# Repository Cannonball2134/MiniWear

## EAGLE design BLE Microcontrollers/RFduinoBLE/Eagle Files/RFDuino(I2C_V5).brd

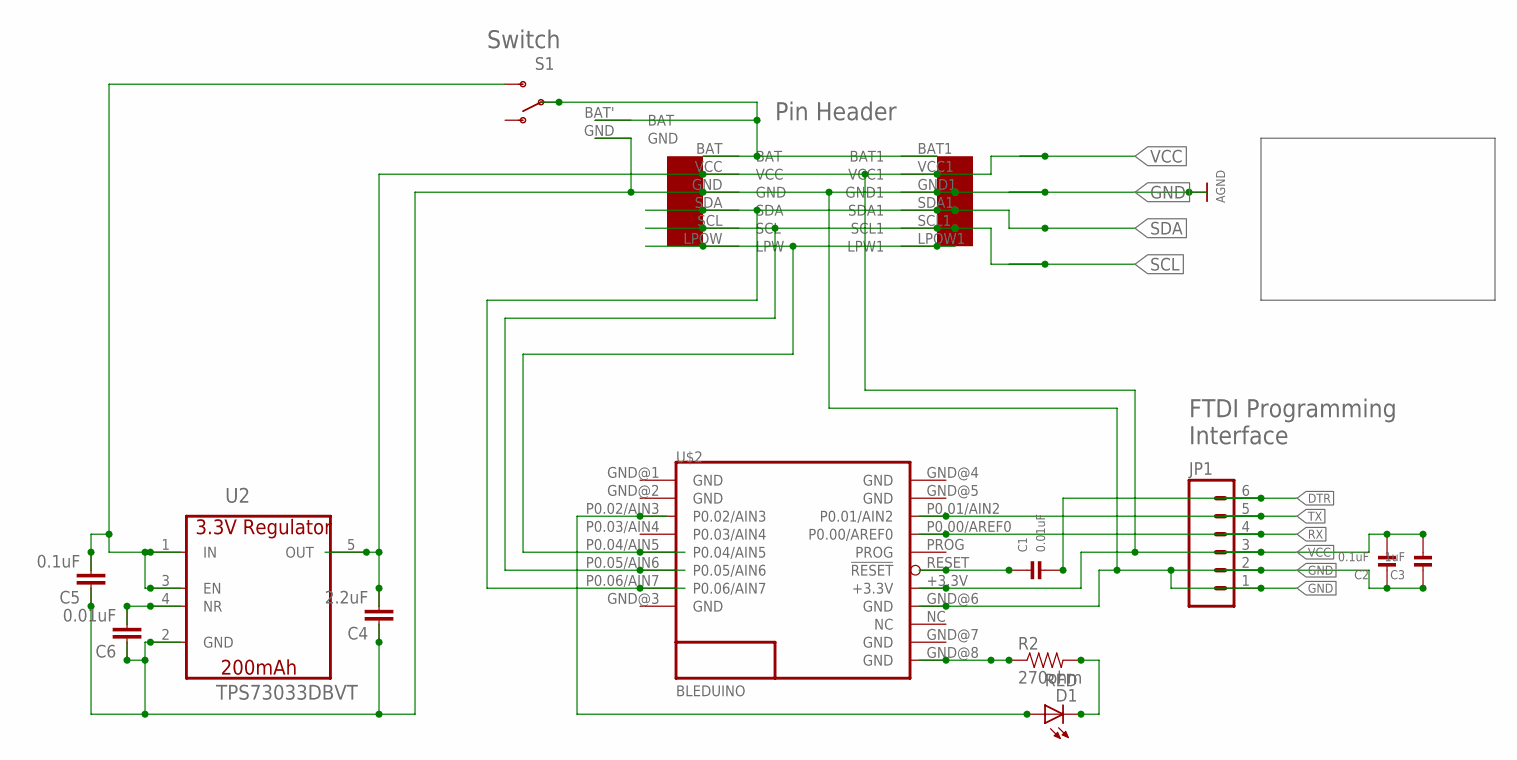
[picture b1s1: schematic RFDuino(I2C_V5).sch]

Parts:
C1: 0.01uF; 0402
C2: 0.1uF; 0402
C3: 1uF; 0402
C4: 2.2uF; 0402-CAP
C5: 0.1uF; 0402-CAP
C6: 0.01uF; 0402-CAP
D1: RED; LED-0603
JP1: M06SIP; 1X06
R2: 270ohm; 0402-RES
S1: SWITCH-SPDT-SMD-A; SWITCH-SPST-SMD-A
U2: TPS73033DBVT; SOT95P290X145-5N
U$1: EZ-I2CHEADERV1
U$2: BLEDUINO
U$4: MINI_BATTERY_HOLES

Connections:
BAT: S1.2, U$1.BAT, U$1.BAT1, U$4.BAT' (BAT)
BAT_INPUT: C5.2, S1.3 (S), U2.1 (IN), U2.3 (EN)
DTR: C1.2, JP1.6
GND: C2.1, C3.1, C4.1, C5.1, C6.1, JP1.1, JP1.2, U2.2 (GND), U$1.GND, U$1.GND1, U$2.GND@6 (GND), U$4.GND
LPW: U$1.LPOW (LPW), U$1.LPOW1 (LPW1), U$2.P0.04/AIN5
unnamed: C1.1, U$2.RESET (!RESET)
unnamed: D1.A, U$2.P0.02/AIN3
unnamed: C6.2, U2.4 (NR)
unnamed: D1.C, R2.2
unnamed: R2.1, U$2.GND@8 (GND)
RX: JP1.4, U$2.P0.00/AREF0
SCL: U$1.SCL, U$1.SCL1, U$2.P0.05/AIN6
SDA: U$1.SDA, U$1.SDA1, U$2.P0.06/AIN7
TX: JP1.5, U$2.P0.01/AIN2
VCC: C2.2, C3.2, C4.2, JP1.3, U2.5 (OUT), U$1.VCC, U$1.VCC1, U$2.+3.3V

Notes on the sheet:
Switch
Pin Header
FTDI Programming Interface

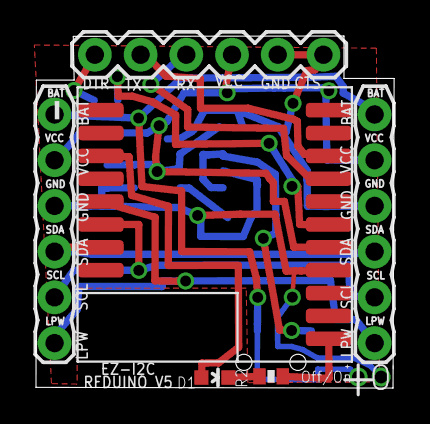
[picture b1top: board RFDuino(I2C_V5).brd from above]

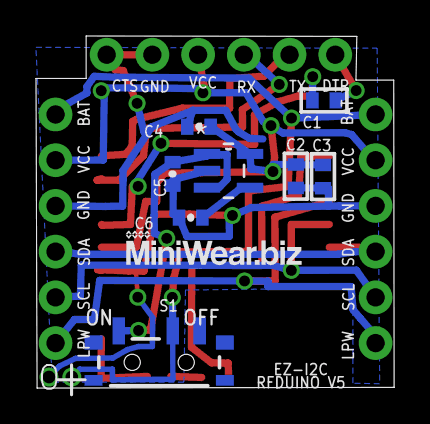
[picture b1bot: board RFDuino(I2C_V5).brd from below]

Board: 2 copper layers, 19.9 x 19.6 mm, 15 parts (9 on the bottom side), 15 nets.

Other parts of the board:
U$3: LOGO2

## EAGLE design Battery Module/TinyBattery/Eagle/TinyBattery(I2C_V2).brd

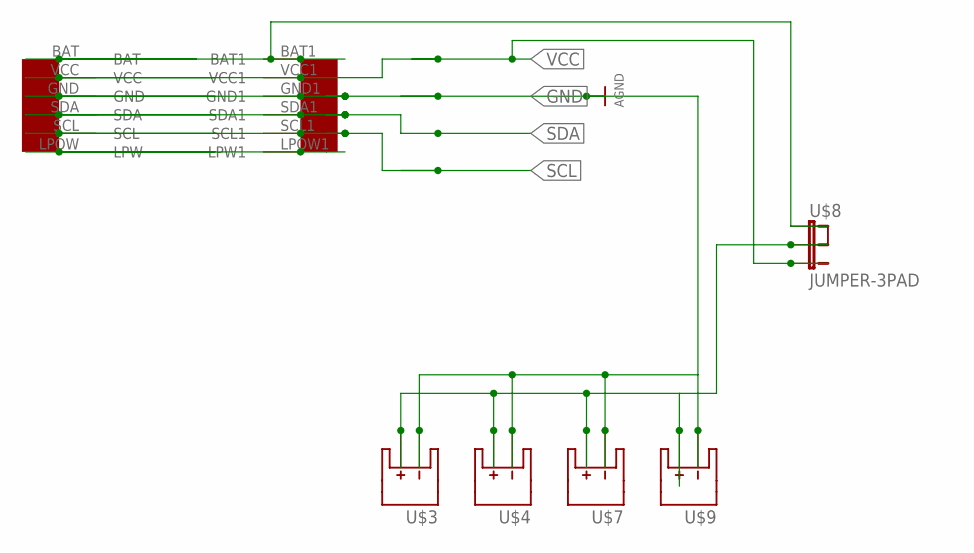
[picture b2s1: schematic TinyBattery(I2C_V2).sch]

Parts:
U$1: EZ-I2CHEADERV1
U$3, U$4, U$7, U$9: BATTERY_1.25MM_PINHOLES
U$8: JUMPER-3PAD

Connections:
BAT: U$1.BAT, U$1.BAT1, U$8.1
GND: U$1.GND, U$1.GND1, U$3.-, U$4.-, U$7.-, U$9.-
unnamed: U$3.+, U$4.+, U$7.+, U$8.2, U$9.+
unnamed: U$1.LPOW (LPW), U$1.LPOW1 (LPW1)
SCL: U$1.SCL, U$1.SCL1
SDA: U$1.SDA, U$1.SDA1
VCC: U$1.VCC, U$1.VCC1, U$8.3

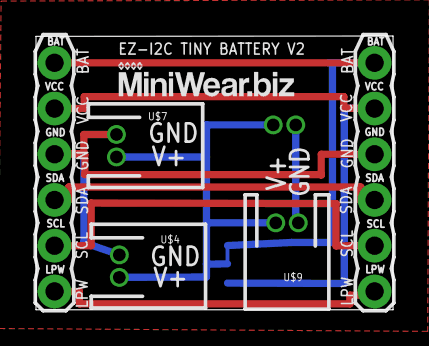
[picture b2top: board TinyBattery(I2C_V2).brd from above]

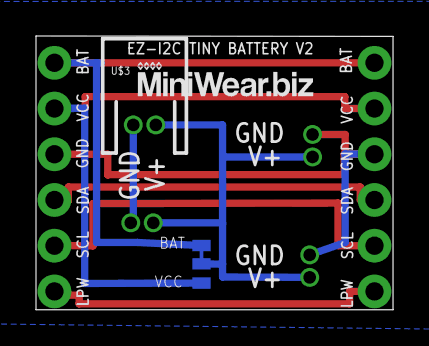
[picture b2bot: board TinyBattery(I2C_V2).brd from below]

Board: 2 copper layers, 19.8 x 15.2 mm, 8 parts (3 on the bottom side), 7 nets.

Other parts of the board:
U$2, U$6: LOGO2

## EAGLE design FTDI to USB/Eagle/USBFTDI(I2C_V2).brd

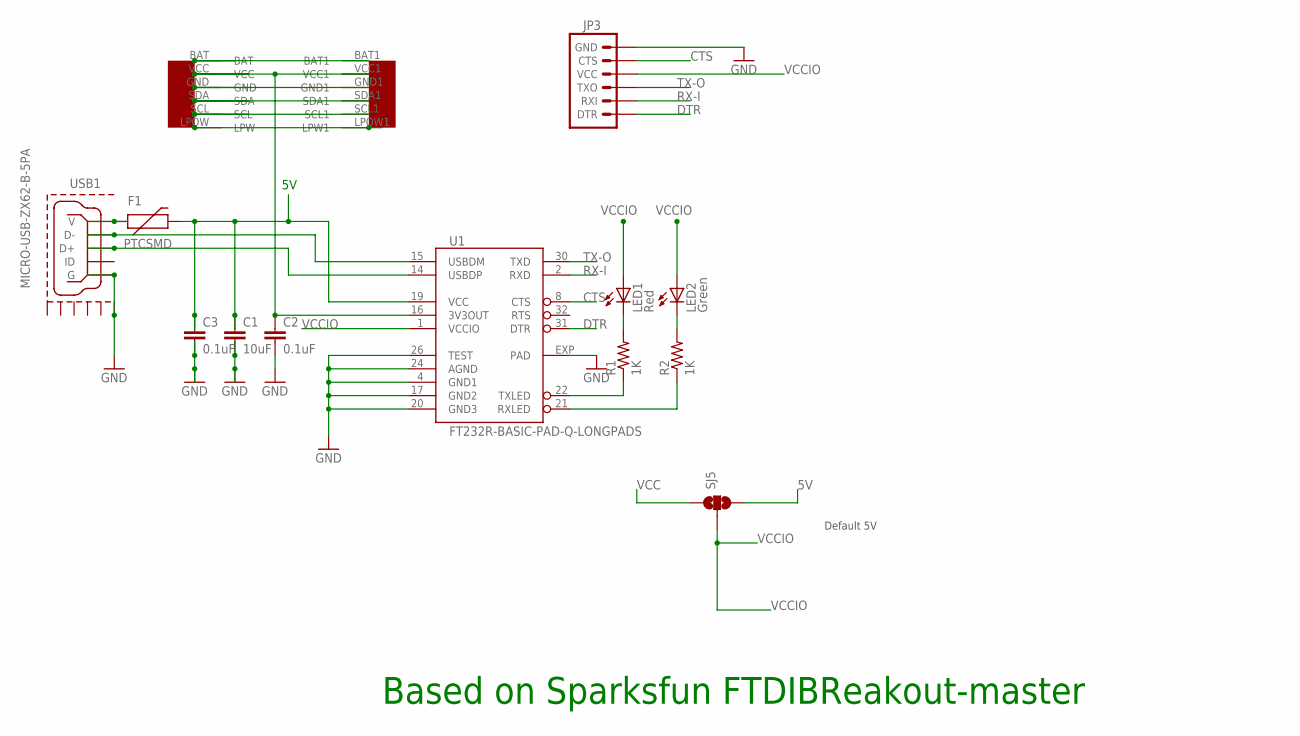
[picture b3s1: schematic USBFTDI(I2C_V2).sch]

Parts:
C1: 10uF; 0402-CAP
C2, C3: 0.1uF; 0402-CAP
F1: PTCSMD; PTC-1206
JP3: ARDUINO_SERIAL_PROGRAMPTH; 1X06
LED1: Red; LED-0603
LED2: Green; LED-0603
R1, R2: 1K; R0402
SJ5: SOLDERJUMPER_2WAY-LEFT-BRIDGED; SJ-3-LEFT
U1: FT232R-BASIC-PAD-Q-LONGPADS; QFN32-LONG
U$1: EZ-I2CHEADERV1
USB1: MICRO-USB-ZX62-B-5PA; ZX62-B-5PA

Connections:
5V: C1.1, C3.1, F1.2, SJ5.3, U1.19 (VCC)
BAT: U$1.BAT, U$1.BAT1
CTS: JP3.5 (CTS), U1.8 (CTS)
DTR: JP3.1 (DTR), U1.31 (DTR)
GND: C1.2, C2.2, C3.2, JP3.6 (GND), U1.4 (GND1), U1.17 (GND2), U1.20 (GND3), U1.24 (AGND), U1.26 (TEST), U1.EXP (PAD), U$1.GND, U$1.GND1, USB1.5 (G), USB1.GND@6 (GND6)
GND1: USB1.GND@1 (GND1)
GND2: USB1.GND@2 (GND2)
GND3: USB1.GND@3 (GND3)
GND4: USB1.GND@4 (GND4)
GND5: USB1.GND@5 (GND5)
LPW: U$1.LPOW (LPW), U$1.LPOW1 (LPW1)
unnamed: U1.14 (USBDP), USB1.3 (D+)
unnamed: U1.15 (USBDM), USB1.2 (D-)
unnamed: R2.1, U1.21 (RXLED)
unnamed: F1.1, USB1.1 (V)
unnamed: LED1.C, R1.2
unnamed: LED2.C, R2.2
unnamed: R1.1, U1.22 (TXLED)
RX-I: JP3.2 (RXI), U1.2 (RXD)
SCL: U$1.SCL, U$1.SCL1
SDA: U$1.SDA, U$1.SDA1
TX-O: JP3.3 (TXO), U1.30 (TXD)
VCC: C2.1, SJ5.1, U1.16 (3V3OUT), U$1.VCC, U$1.VCC1
VCCIO: JP3.4 (VCC), LED1.A, LED2.A, SJ5.2, U1.1 (VCCIO)

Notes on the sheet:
Based on Sparksfun FTDIBReakout-master
Default 5V
VCCIO

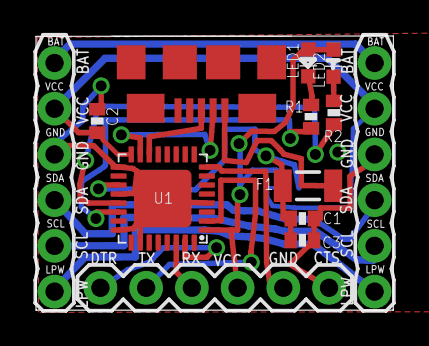
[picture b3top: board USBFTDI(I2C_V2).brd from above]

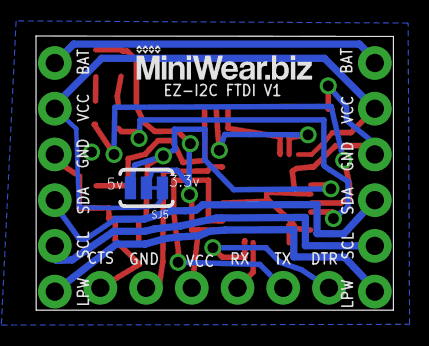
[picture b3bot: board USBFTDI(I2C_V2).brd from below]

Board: 2 copper layers, 19.9 x 15.2 mm, 14 parts (2 on the bottom side), 19 nets.

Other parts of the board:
U$3: LOGO2

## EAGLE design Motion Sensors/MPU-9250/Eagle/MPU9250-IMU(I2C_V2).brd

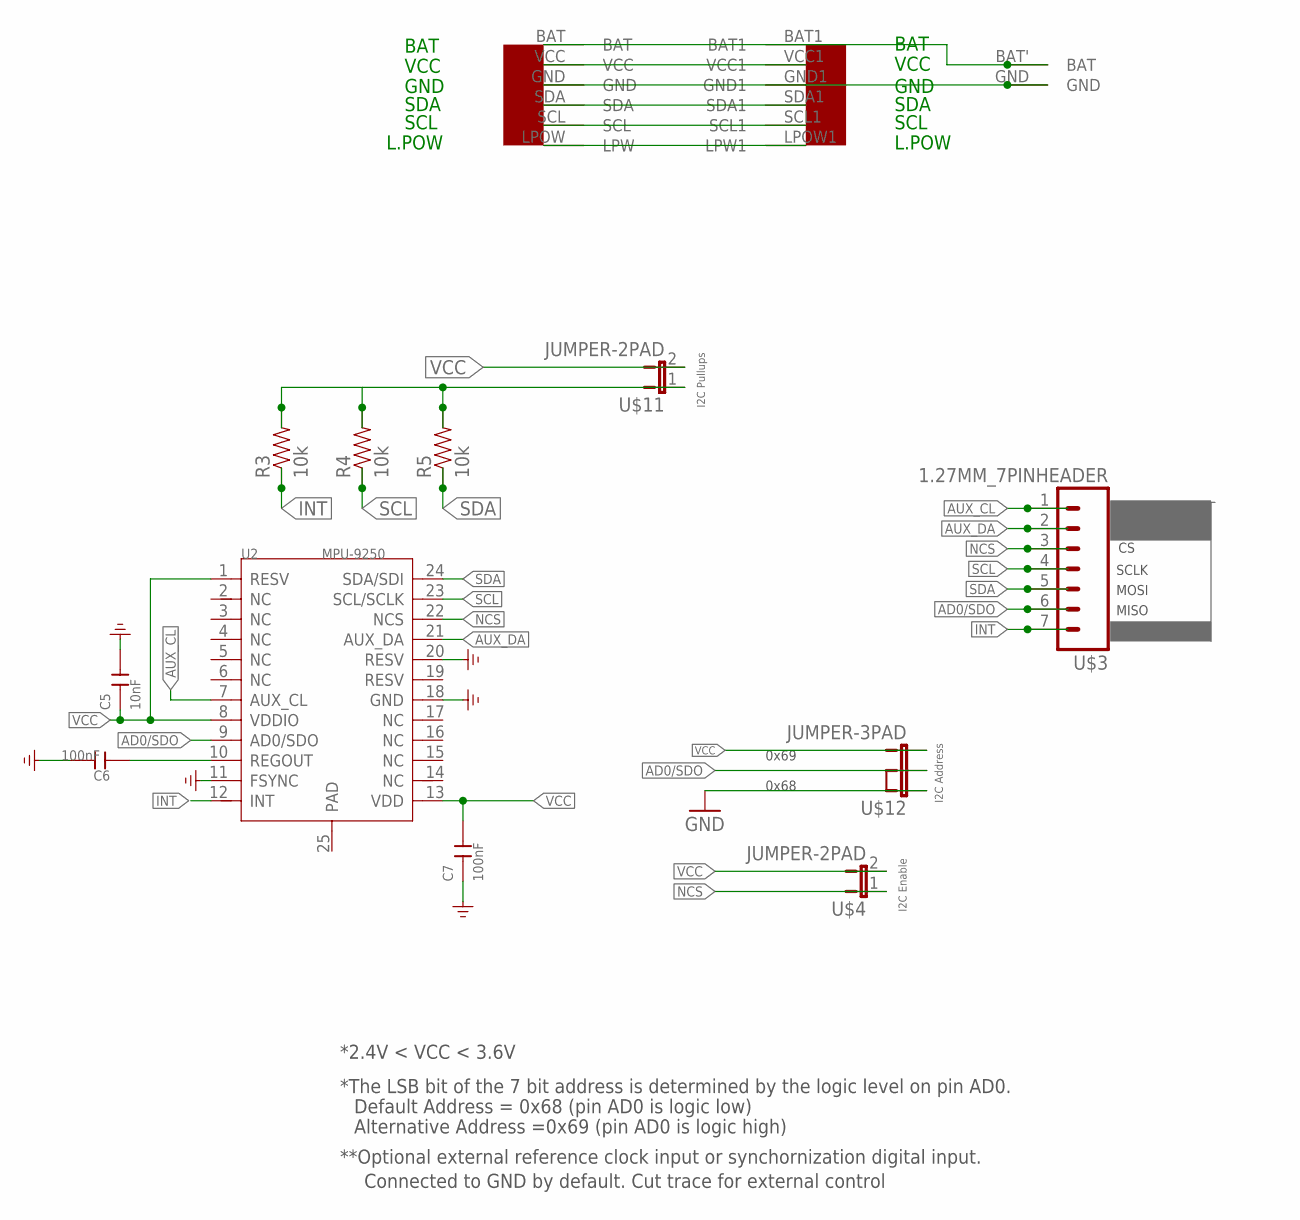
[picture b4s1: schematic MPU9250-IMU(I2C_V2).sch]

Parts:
C5: 10nF; C0603
C6, C7: 100nF; C0603
R3, R4, R5: 10k; 0402-RES
U2: MPU-9250; LEAD-QFN24
U$1: EZ-I2CHEADERV1
U$3: 1.27MM_7PINHEADER
U$4, U$11: JUMPER-2PAD
U$10: MINI_BATTERY_HOLES
U$12: JUMPER-3PAD

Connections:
AD0/SDO: U2.9 (AD0/SDO), U$3.6, U$12.2
AUX_CL: U2.7 (AUX_CL), U$3.1
AUX_DA: U2.21 (AUX_DA), U$3.2
BAT: U$1.BAT, U$1.BAT1, U$10.BAT' (BAT)
GND: C5.2, C6.2, C7.1, U2.11 (FSYNC), U2.18 (GND), U2.20 (RESV), U$1.GND, U$1.GND1, U$10.GND, U$12.1
INT: R3.1, U2.12 (INT), U$3.7
unnamed: C6.1, U2.10 (REGOUT)
unnamed: U$1.LPOW (LPW), U$1.LPOW1 (LPW1)
unnamed: R3.2, R4.2, R5.2, U$11.1
NCS: U2.22 (NCS), U$3.3, U$4.1
SCL: R4.1, U2.23 (SCL/SCLK), U$1.SCL, U$1.SCL1, U$3.4
SDA: R5.1, U2.24 (SDA/SDI), U$1.SDA, U$1.SDA1, U$3.5
VCC: C5.1, C7.2, U2.1 (RESV), U2.8 (VDDIO), U2.13 (VDD), U$1.VCC, U$1.VCC1, U$4.2, U$11.2, U$12.3

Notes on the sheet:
**Optional external reference clock input or synchornization digital input.
Connected to GND by default. Cut trace for external control
Default Address = 0x68 (pin AD0 is logic low)
Alternative Address =0x69 (pin AD0 is logic high)
*The LSB bit of the 7 bit address is determined by the logic level on pin AD0.
*2.4V < VCC < 3.6V
VCC
GND
SDA
SCL
BAT
L.POW
0x69
0x68
SCLK
MOSI
MISO
I2C Address
I2C Enable
I2C Pullups

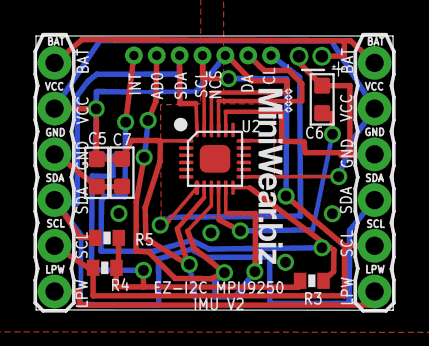
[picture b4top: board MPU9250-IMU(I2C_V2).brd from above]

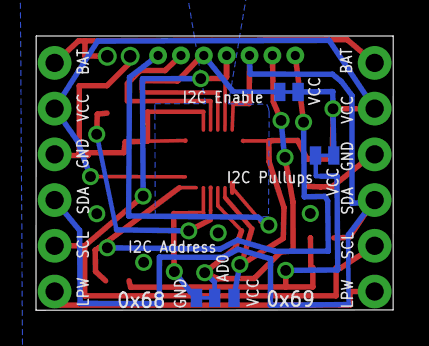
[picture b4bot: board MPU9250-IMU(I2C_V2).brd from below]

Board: 2 copper layers, 19.8 x 15.2 mm, 14 parts (3 on the bottom side), 13 nets.

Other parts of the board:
U$2: LOGO2

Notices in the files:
parts and their libraries:
SparkFun-Connectors: Licensing: CC v3.0 Share-Alike You are welcome to use this library for commercial purposes.
microbuilder: This work is placed in the public domain, and may be freely used for commercial and non-commercial work with the following conditions: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
